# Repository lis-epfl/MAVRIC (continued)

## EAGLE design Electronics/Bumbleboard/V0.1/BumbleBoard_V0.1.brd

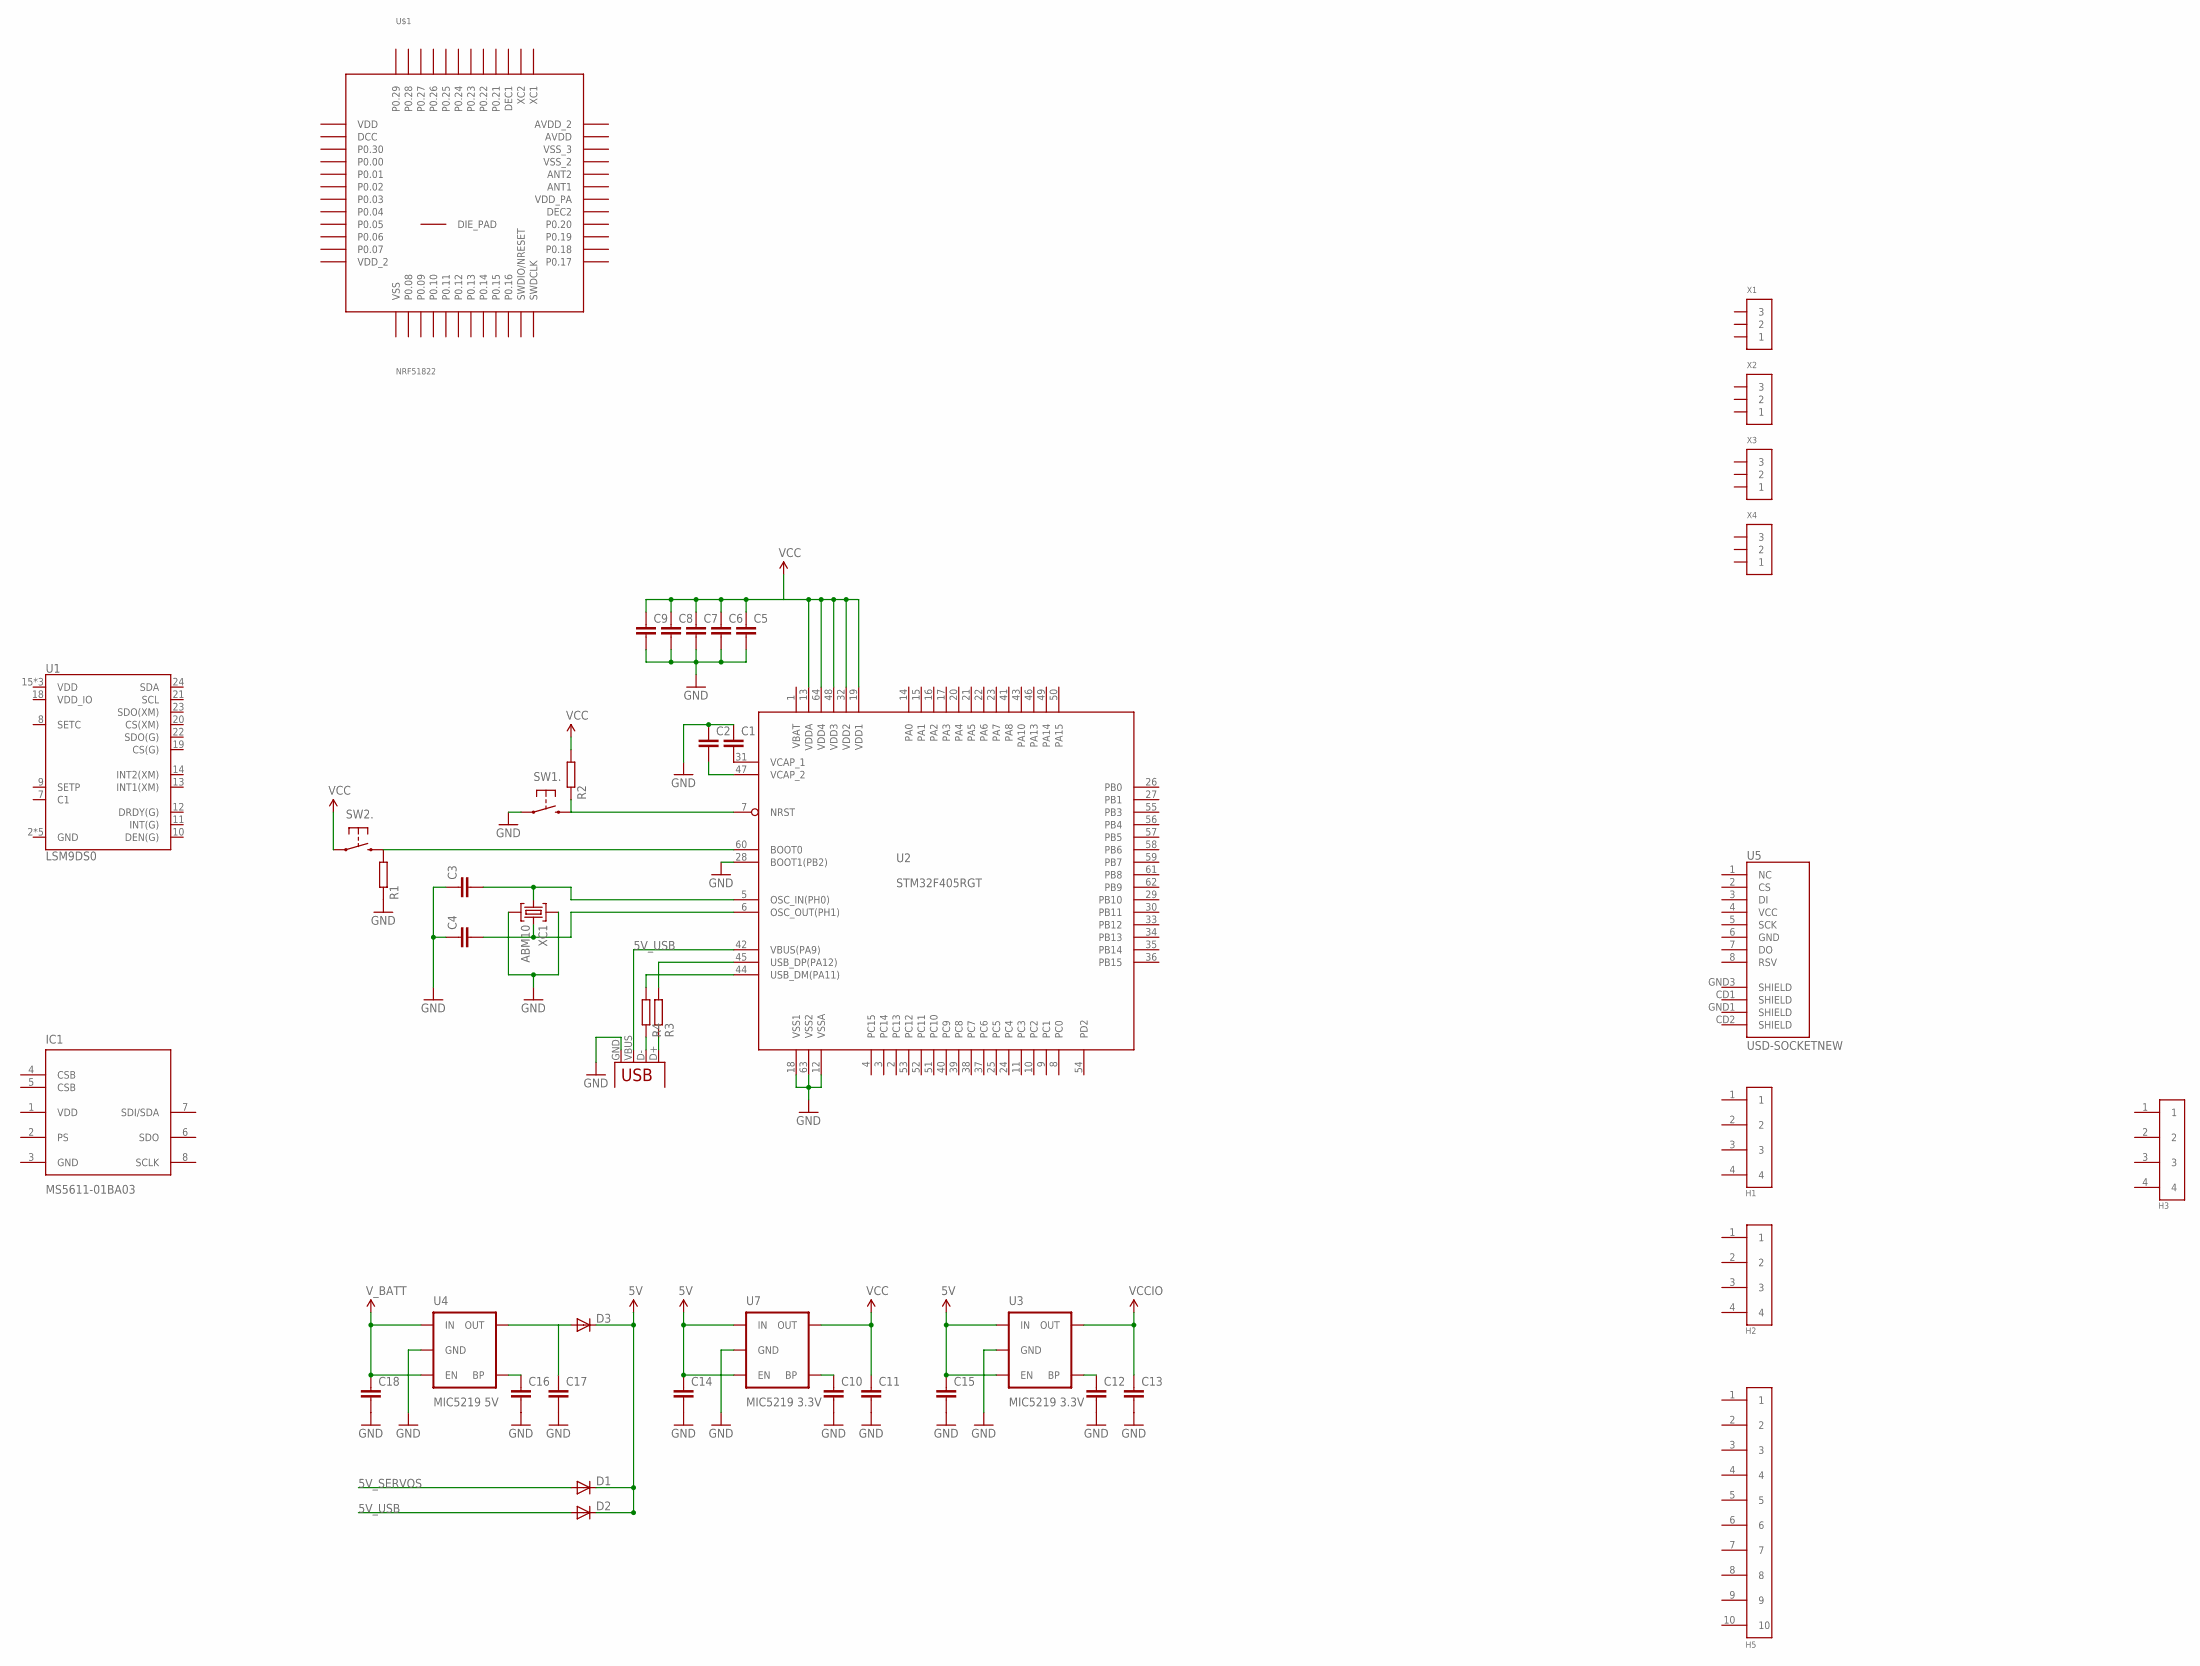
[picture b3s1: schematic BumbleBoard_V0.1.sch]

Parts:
C1, C2, C3, C4, C5, C6, C7, C8, C9, C10, C12, C16: CAP0402-CAP; 0402-CAP
C11, C13, C14, C15, C17, C18: CAP0603-CAP; 0603-CAP
D1, D2, D3: DIODESOD; SOD-323
H1, H2, H3: CON_4; CON1.27_4
H5: CON_10; CON1.27_10
IC1: MS5611-01BA03; SON125P300X500X100-8N
R1, R2, R3, R4: RESISTOR-0402; 0402-RES
SW1, SW2: SWITCH-B3U-1110-BOSS; SWITCH-TACT-B3U-1100P-B
U1: LSM9DS0; LGA-24
U2: STM32F405RGT; LQFP64
U3, U7: MIC5219 3.3V; SOT23-5
U4: MIC5219 5V; SOT23-5
U5: USD-SOCKETNEW; MICRO-SD-SOCKET-PP
U$1: NRF51822; QFN48
X1, X2, X3, X4: CONN_3-1-53047; PB-53047-03
X5: USB-MICROB
XC1: ABM10

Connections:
5V: C14.1, C15.1, D1.1 (C), D2.1 (C), D3.1 (C), U3.1 (IN), U3.3 (EN), U7.1 (IN), U7.3 (EN)
5V_SERVOS: D1.2 (A)
5V_USB: D2.2 (A), U2.42 (VBUS(PA9)), X5.VBUS
GND: C1.1, C2.1, C3.1, C4.1, C5.2, C6.2, C7.2, C8.2, C9.2, C10.2, C11.2, C12.2, C13.2, C14.2, C15.2, C16.2, C17.2, C18.2, IC1.3 (GND), R1.P$1 (1), SW1.1, U2.12 (VSSA), U2.18 (VSS1), U2.28 (BOOT1(PB2)), U2.63 (VSS2), U3.2 (GND), U4.2 (GND), U7.2 (GND), X5.GND, XC1.2, XC1.4
unnamed: C1.2, U2.31 (VCAP_1)
unnamed: C2.2, U2.47 (VCAP_2)
unnamed: R1.P$2 (2), SW2.2, U2.60 (BOOT0)
unnamed: R2.P$1 (1), SW1.2, U2.7 (NRST)
unnamed: R4.P$1 (1), X5.D-
unnamed: C3.2, U2.5 (OSC_IN(PH0)), XC1.1
unnamed: C4.2, U2.6 (OSC_OUT(PH1)), XC1.3
unnamed: R3.P$1 (1), X5.D+
unnamed: R3.P$2 (2), U2.45 (USB_DP(PA12))
unnamed: R4.P$2 (2), U2.44 (USB_DM(PA11))
unnamed: C10.1, U7.4 (BP)
unnamed: C12.1, U3.4 (BP)
unnamed: C16.1, U4.4 (BP)
unnamed: C17.1, D3.2 (A), U4.5 (OUT)
VBAT: U2.1 (VBAT)
VCC: C5.1, C6.1, C7.1, C8.1, C9.1, C11.1, R2.P$2 (2), SW2.1, U2.13 (VDDA), U2.19 (VDD1), U2.32 (VDD2), U2.48 (VDD3), U2.64 (VDD4), U7.5 (OUT)
VCCIO: C13.1, U3.5 (OUT)
VDD: IC1.1 (VDD)
V_BATT: C18.1, U4.1 (IN), U4.3 (EN)

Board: 2 copper layers, 45 parts (4 on the bottom side), 20 nets, no tracks yet.

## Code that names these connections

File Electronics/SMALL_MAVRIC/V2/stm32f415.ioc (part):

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Mcu.Name=STM32F415RGTx
Mcu.Package=LQFP64
Mcu.UserName=STM32F415RGTx
PA0-WKUP.Mode=Asynchronous
PA0-WKUP.Signal=UART4_TX
PA1.Mode=Asynchronous
PA1.Signal=UART4_RX
PA10.Mode=OTG/Dual_Role_Device
PA10.Signal=USB_OTG_FS_ID
PA11.Mode=OTG/Dual_Role_Device
PA11.Signal=USB_OTG_FS_DM
PA12.Mode=OTG/Dual_Role_Device
PA12.Signal=USB_OTG_FS_DP
PA15.Signal=GPIO_Output
PA2.Mode=Asynchronous
PA2.Signal=USART2_TX
PA3.Mode=Asynchronous
PA3.Signal=USART2_RX
PA4.Signal=GPIO_Output
PA5.Signal=ADCx_IN5
PA6.Signal=ADCx_IN6
PA7.Signal=ADCx_IN7
PA9.Mode=Activate_VBUS
PA9.Signal=USB_OTG_FS_VBUS
PB10.Mode=I2C
PB10.Signal=I2C2_SCL
PB11.Mode=I2C
PB11.Signal=I2C2_SDA
PB12.Mode=Slave
PB12.Signal=CAN2_RX
PB13.Mode=Slave
PB13.Signal=CAN2_TX
PB3.Signal=S_TIM2_CH2
PB4.Signal=S_TIM3_CH1
PB5.Signal=S_TIM3_CH2
PB6.Signal=S_TIM4_CH1
PB7.Signal=S_TIM4_CH2
PB8.Signal=S_TIM4_CH3
PC10.Mode=SD_4_bits_Wide_bus
PC10.Signal=SDIO_D2
PC11.Mode=SD_4_bits_Wide_bus
PC11.Signal=SDIO_D3
PC12.Mode=SD_4_bits_Wide_bus
PC12.Signal=SDIO_CK
PC14-OSC32_IN.Signal=GPIO_Output
PC15-OSC32_OUT.Signal=GPIO_Output
PC4.Signal=ADCx_IN14
PC8.Mode=SD_4_bits_Wide_bus
PC8.Signal=SDIO_D0
PC9.Mode=SD_4_bits_Wide_bus
PC9.Signal=SDIO_D1
PD2.Mode=SD_4_bits_Wide_bus
PD2.Signal=SDIO_CMD
PH0-OSC_IN.Mode=HSE-External-Oscillator
PH0-OSC_IN.Signal=RCC_OSC_IN
PH1-OSC_OUT.Mode=HSE-External-Oscillator
PH1-OSC_OUT.Signal=RCC_OSC_OUT
RCC.HSE_VALUE=25000000
RCC.SYSCLKFreq_VALUE=16000000

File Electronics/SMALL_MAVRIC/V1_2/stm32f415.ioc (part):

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Mcu.Name=STM32F415RGTx
Mcu.Package=LQFP64
Mcu.UserName=STM32F415RGTx
PA0-WKUP.Mode=Asynchronous
PA0-WKUP.Signal=UART4_TX
PA1.Mode=Asynchronous
PA1.Signal=UART4_RX
PA10.Mode=OTG/Dual_Role_Device
PA10.Signal=USB_OTG_FS_ID
PA11.Mode=OTG/Dual_Role_Device
PA11.Signal=USB_OTG_FS_DM
PA12.Mode=OTG/Dual_Role_Device
PA12.Signal=USB_OTG_FS_DP
PA15.Signal=S_TIM2_CH1_ETR
PA2.Mode=Asynchronous
PA2.Signal=USART2_TX
PA3.Mode=Asynchronous
PA3.Signal=USART2_RX
PA4.Signal=ADCx_IN4
PA5.Mode=Full_Duplex_Master
PA5.Signal=SPI1_SCK
PA6.Signal=ADCx_IN6
PA7.Signal=ADCx_IN7
PA8.Signal=S_TIM1_CH1
PA9.Mode=Activate_VBUS
PA9.Signal=USB_OTG_FS_VBUS
PB0.Signal=ADCx_IN8
PB1.Signal=S_TIM3_CH4
PB10.Mode=I2C
PB10.Signal=I2C2_SCL
PB11.Mode=I2C
PB11.Signal=I2C2_SDA
PB12.Mode=NSS_Signal_Hard
PB12.Signal=SPI2_NSS
PB13.Mode=Full_Duplex_Master
PB13.Signal=SPI2_SCK
PB14.Signal=S_TIM12_CH1
PB15.Signal=S_TIM12_CH2
PB3.Signal=S_TIM2_CH2
PB4.Mode=Full_Duplex_Master
PB4.Signal=SPI1_MISO
PB5.Mode=Full_Duplex_Master
PB5.Signal=SPI1_MOSI
PB6.Mode=I2C
PB6.Signal=I2C1_SCL
PB7.Mode=I2C
PB7.Signal=I2C1_SDA
PB8.Mode=Master
PB8.Signal=CAN1_RX
PB9.Mode=Master
PB9.Signal=CAN1_TX
PC10.Mode=SD_4_bits_Wide_bus
PC10.Signal=SDIO_D2
PC11.Mode=SD_4_bits_Wide_bus
PC11.Signal=SDIO_D3
PC12.Mode=SD_4_bits_Wide_bus
PC12.Signal=SDIO_CK
PC2.Mode=Full_Duplex_Master
PC2.Signal=SPI2_MISO
PC3.Mode=Full_Duplex_Master
PC3.Signal=SPI2_MOSI
PC6.Mode=Asynchronous
PC6.Signal=USART6_TX
PC7.Mode=Asynchronous
PC7.Signal=USART6_RX
PC8.Mode=SD_4_bits_Wide_bus
PC8.Signal=SDIO_D0
PC9.Mode=SD_4_bits_Wide_bus
PC9.Signal=SDIO_D1
PD2.Mode=SD_4_bits_Wide_bus
PD2.Signal=SDIO_CMD
RCC.HSE_VALUE=25000000
RCC.SYSCLKFreq_VALUE=16000000

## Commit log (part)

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2014-09-02 Update LICENSE
2014-09-02 Started to add submodules
2014-09-03 Update MAVRIC_Documentation
2014-09-03 Update submodule MAVRIC_Mechanics
2014-09-03 Update submodule MAVRIC_Utilities
2014-09-03 Removed link to Bumblebot
2014-09-03 Add Readme for Documentation
2014-09-03 Remove default web page
2014-09-03 Update wiki and latex documentation
2014-09-04 Update DFU bat script examples regarding the new folder organisation
2014-09-10 Added esc_holder.stl
2014-09-26 add pairing widget
2014-09-29 modify Xbee folder from doc to utility folder
2014-10-03 Add the widget to perform on-the-go calibration
2014-10-09 Fixed bug with newer python version
2014-12-04 Add datasheet for I2CXL sonar
2014-12-09 Config files
2014-12-18 adding readme file
2015-01-05 finish updating LEQuqd example code
2015-01-05 missing init for position telemetry plus change function order to properly init in sim mode
2015-01-13 Fix Codelite project for LEQuad
2015-01-13 update remote binding widget with the param4 values set to 11 by default, which correspond to protocol DSM2 11bits channel encoding
2015-01-13 [Joystick] update navigation init and joystick init
2015-01-14 Update doc submodule
2015-01-14 dd gitignore for latex folder
2015-01-20 Removed mavlink submodule
2015-01-29 add sonar_i2c_xl capability
2015-02-10 Sarted hal reformating
2015-02-11 Fixed some compilation issues
2015-02-16 add symbolic link script
2015-02-16 adapt LEQuad to last library updates
2015-03-03 Added the avr32-toolchain to Utilities folder
2015-03-17 updating acording to last merge with battery checks
2015-03-18 udpate task to yaw_relatif according to last merge
2015-03-23 Add avr32 Makefile
2015-03-23 Forgot two assembly files in Makefile
2015-03-23 Update asf
2015-03-23 Add dfu_program.sh
2015-03-23 Start resolving conflicts
2015-03-24 Update project
2015-03-24 Fix mess with link to LIbrary
2015-04-15 Renamed *.c => *.cpp: boardsupport, central_data, mavlink_telemetry, and tasks
2015-04-16 [Project changes !] Many changes for cross platform HAL (WIP) - moved drivers from hal/ to drivers/ - added folder hal/common for common HAL interfaces - added C++ interface for I2C - added I2C imple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
    Many changes in the project to make it work
    - central_data is a C++ class
    - central data has a member 'board' of type megafly_rev4
    - central_data constructor first calls the old boardsupport init, then the new boa
2015-04-20 Use .hpp for C++ headers
2015-05-08 Added custom widgets follwing the new way to design them
2015-05-20 New qml files for remote binding
2015-05-26 Xbee RX ok, not so well for TX
2015-05-29 update electronic
2015-05-29 update according to library architecture changes
2015-06-10 update according to last pull request
2015-06-16 removed compilation bug
2015-06-16 fin test
2015-06-17 Fix issues after merge
2015-06-22 add lsm330 driver
2015-07-02 adapt to new C++ adaptation in the library
2015-07-14 general commit
2015-07-15 mecha update
2015-07-20 update init according to the 2 last pull requests.
2015-07-23 update with Przemek board
2015-07-23 cosmetics
2015-07-24 fix compilation issue
2015-07-27 Serial interface for udp sockets on linux
2015-08-05 fixed reference to MAVRIC_Library submodule
    MAVRIC is now pointing to the most recent version of MAVRIC_Library/master
2015-08-07 Added configuration file for GPS u_blox lea 6h
2015-08-07 Added XBee datasheet
2015-08-07 Added protocol specification for UBLOX
2015-08-10 Added testing for remote callbacks
2015-08-14 Lab_B stuff: added filters, cleaned code and changed estimator_pitch structure
2015-08-14 Lab_B: changed variable names; complementary filter now working
2015-08-19 Added Source mode as onboard parameter in order to be able to use the joystick
2015-08-19 Lab_B: added imu_lab_b stuff and further changes
2015-08-20 Lab_B: changed imu_lab from scaled to raw; changed filter of imu_lab_b and switched off mavlink messages
2015-08-20 Lab_B changed pitch_estimator to use imu_lab_b; fixed imu_lab: gyro is now also updated
2015-08-20 Lab_B changed to new config file
2015-08-21 Lab_B: changed arguments of estimate_pitch_gyro: removed gyro_y_old from arguments
    This means we change the integration from trapezoidal to stairs
2015-08-21 Removed functions for students to fill
2015-08-24 changing usb port from otg_HS to otg_FS
2015-08-25 removed the Release folder from the tracking
2015-08-25 Modified for the use of LE QUAD #150.
2015-08-27 Updated lab_b
2015-08-27 remove some useless include to ease portability
2015-08-27 Changed MAVRIC_Library to most recent version
    Changed Library to commit:
    c36c1884953e6aba5f6e6972348ef3218ada5695
    from 27.08.2015
2015-09-10 removed trace of epuck project files since they are auto regenerated
2015-09-25 - conf_platform: Add definitions for the wing servos pins
2015-09-25 - central_data: Replace and init the stabilisation module and the servo mix with the new ones for the wing - tasks: Update behavior in the different modes to use wing stabilisation function (at this 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
2015-09-29 Adjusted Makefile to detect changes in header files
    - Added -MD -MP switches to ASFLAGS to produce dependency files (*.d) while compiling
    - Removed -MF switch from CFLAGS and CXXFLAGS to produce dependency files (-MD -MP are already there)
    - Created DEPS variable containing existing dependency files (*.d) and include it
    - Added DEPS to files to be deleted by make clean
    - Added default target 'all' (otherwise 'make' would execute target from the dependency files)
    - Cosmetics: removed '/' at the end of $(MAVRIC_LIBS) and $(MAVRIC_SRCS); Before we had paths 'src//config'; this did not produce errors, but is a risk
2015-09-30 - conf_platform: Add defines to select the type of the aircraft (copter or wing), temporary used to select which arm method to use.
2015-09-30 Added a qml file (custom widget) for QGroundControl in order to launch the configuration of the GPS
2015-10-02 Add projects files
2015-10-04 New parameters added to control tuning via qgroundcontrol.
2015-10-05 Update mavlink in Library
2015-10-06 Add GPIO for avr32, make Spektrum_satellite use Gpio interface
2015-10-07 add SMA and launch_detection to Makefile
2015-10-07 disable launch_detection if in flight
2015-10-07 Changes to remove dependency on conf_platform.h from Library modules
2015-10-09 Update qgroundcontrol submodule
2015-10-09 Project changes for branch dev_cpp_manualControl
2015-10-09 Add custom exception.S file
2015-10-09 Removed an unused LIB_SRCS in the Makefile
2015-10-09 Update submodule library
2015-10-09 update central_data.c to remove compiling errors
2015-10-12 Current state for Greg debug
2015-10-12 - Add config file for autopilot 208
2015-10-12 Fix acceleration scale
2015-10-13 Print util writes to usb_serial
2015-10-14 Update configuration for launch_detection module
2015-10-15 Update mavlink_telemetry.c
    add gps_telemetry_init, otherwise gps_config and so on fail !!
2015-10-18 - mavlink_telemetry: Log parameters for attitude tuning - tasks: Add attitude control mode
2015-10-19 Changed main.cpp to include example of debug/console functions
2015-10-20 Makefile, main, Library: added file.cpp and serial.cpp to Makefile, updated example in main.cpp and updated library
2015-10-20 Makefile: fixed typo in linker flags which rendered half of the flags useless
    in LEQuad/avr32_proj/Makefile: changed LDGLAGS to LDFLAGS
    No consequences in the executable
2015-10-20 Makefile: removed useless flags '-Wl,--start-group' and '-Wl,--end-group' and '-Lsrc/asf/.../at32ucr3fp/gcc'
    --start-group: This does not change anything, since only the math library was inside the group
    and the math library has no circulary dependencies
    -Lsrc/asf/.../at32ucr3fp/gcc: not changing anything since:
    a) was not in use before because of typo;
    b) points to a wrong destination (src/ instead of ../src/)
    c) the folder is already in SRCS_INC
2015-10-20 Adapt to new library ( ! compiles but does not work ! )
2015-10-21 Add Link to Library
2015-10-23 Update qml calibration widget
2015-10-27 add logging parameters and onboard parameters for attitude stabilization phase
2015-10-27 Add acceleration to logs
2015-10-27 use analog rail 13 instead for the airspeed, connecting it to the exterior of the PCB
2015-10-28 Log SMA not acc{X,Y,Z}
2015-10-30 - mavlink_telemetry: Added airspeed sensor and GPS logged values and onboard parameters for Madgwick and airspeed sensor - tasks: Madgwick algorithm is now used instead of qfilter
2015-11-02 add angular speeds to log
2015-11-02 Add debug messages
2015-11-02 Replace reference to launch_detection (now in state_machine_custom) and init state_machine_custom
2015-11-02 update state_machine_custom instead of inline
2015-11-03 add ahrs to custom state machine
2015-11-03 add sonar and gps to log
2015-11-04 log sonar and gps speeds
2015-11-04 Update imu config for MAV001 TODO: others
2015-11-06 - central_data: State now needs pointer to airspeed to stop its calibration at arming. Other unused code removed. - mavlink_telemetry: Airspeed parameters updated.
2015-11-09 update logging scheme
2015-11-12 - central_data: Airspeed sensor pointer added in Madgwick (for acceleration compensations) and in stabilisation_wing (for velocity control). - mavlink_telemetry: Updated list of onboard params and lo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
2015-11-13 Change bitfield operation for dedicated functions
2015-11-16 Remove dependency to baro for state_machine_custom
2015-11-19 adapt quad to wing for adaptive morph
2015-11-19 Init reference to ADNS module
2015-11-23 Added wing specific files to Makefile
2015-11-24 comment adns init
2015-11-24 Velocity control on thrust
2015-11-25 Update makefile in avr32 folder
2015-11-25 central_data changes for library
2015-11-27 comment things regarding gps2
2015-11-27 Added manual_control_telemetry to Makefile and its init function to mavlink_telemetry
2015-11-30 Project change for implementation of pwm_servos
2015-11-30 init height control with position hold
2015-11-30 Switch to simulated gps for testing (because of emergency)
2015-12-01 Update MAV calib, sync with Utilities folder
2015-12-02 Calibrations: Updated conf_imu.h
2015-12-02 - central_data: Added vector field waypoint structure.
2015-12-02 - tasks: Correction of vector copy.
2015-12-02 Changed cruise speed of navigation to fit with fix wing platforms
2015-12-03 - mavlink_telemetry: Name of onboard parameter changed - tasks: Now navigation module is called again instead of vector field (vector field is called by the navigation)
2015-12-03 rename state_machine_custom to throw_recovery_state_machine
2015-12-03 Remove dependency stabilisation_copter_default_config.c
2015-12-03 remove adns_init from central_data
2015-12-07 multiple commits, in order to be clean with remote repo
2015-12-07 - tasks: Added possibility to switch between remote in velocity and vector field, using the custom switch of the remote.
2015-12-09 Add config for MAVID 207
2015-12-10 Added dubin.* to Makefile
2015-12-11 Tried to debug analog airspeed
2015-12-11 - central_data: Overwrite config max climb rate for navigation.
2015-12-16 - Parameters and logging values updated.
2015-12-16 update log for DGPS
2015-12-17 - central_data: Navigation is now sent to stabilisation_wing. - mavlink_telemetry: Put new parameters as onboard. - tasks: Clean.
2015-12-18 New onboard param.
2016-01-26 Board megafly4.2 with inverted RX and TX GPS pins
2016-01-26 Update IMU calib files to new format
2016-02-10 adding new eagle file for the small mavric autopilot
2016-02-15 added .qml to test the go home cmd id 20
2016-02-22 change gyro and accelero orientations, according to autopilot attach upside down on that model
2016-02-22 update control mode to be able to select roll vs pitch control and single folding for roll caracterization
2016-02-29 small adjustment
2016-03-25 changes in mecha Inventor
2016-04-15 Added button for north vector calibration also in qml widget
2016-05-09 QGroundControl calibration widget: updated .qgw of calibration widget to match .qml
2016-05-18 Added land on tag qml
2016-05-24 Adding tests files for EKF attitude estimation
2016-06-28 Added dronedome marker holder CAD files
2016-07-22 Update Control_Modes_Nav widget to add the land command. 'Return to home' and 'Stop there' commands commented as not properly working.
2016-08-19 additional projects
